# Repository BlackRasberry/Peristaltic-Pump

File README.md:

# Peristaltic-Pump
An open source peristaltic pump

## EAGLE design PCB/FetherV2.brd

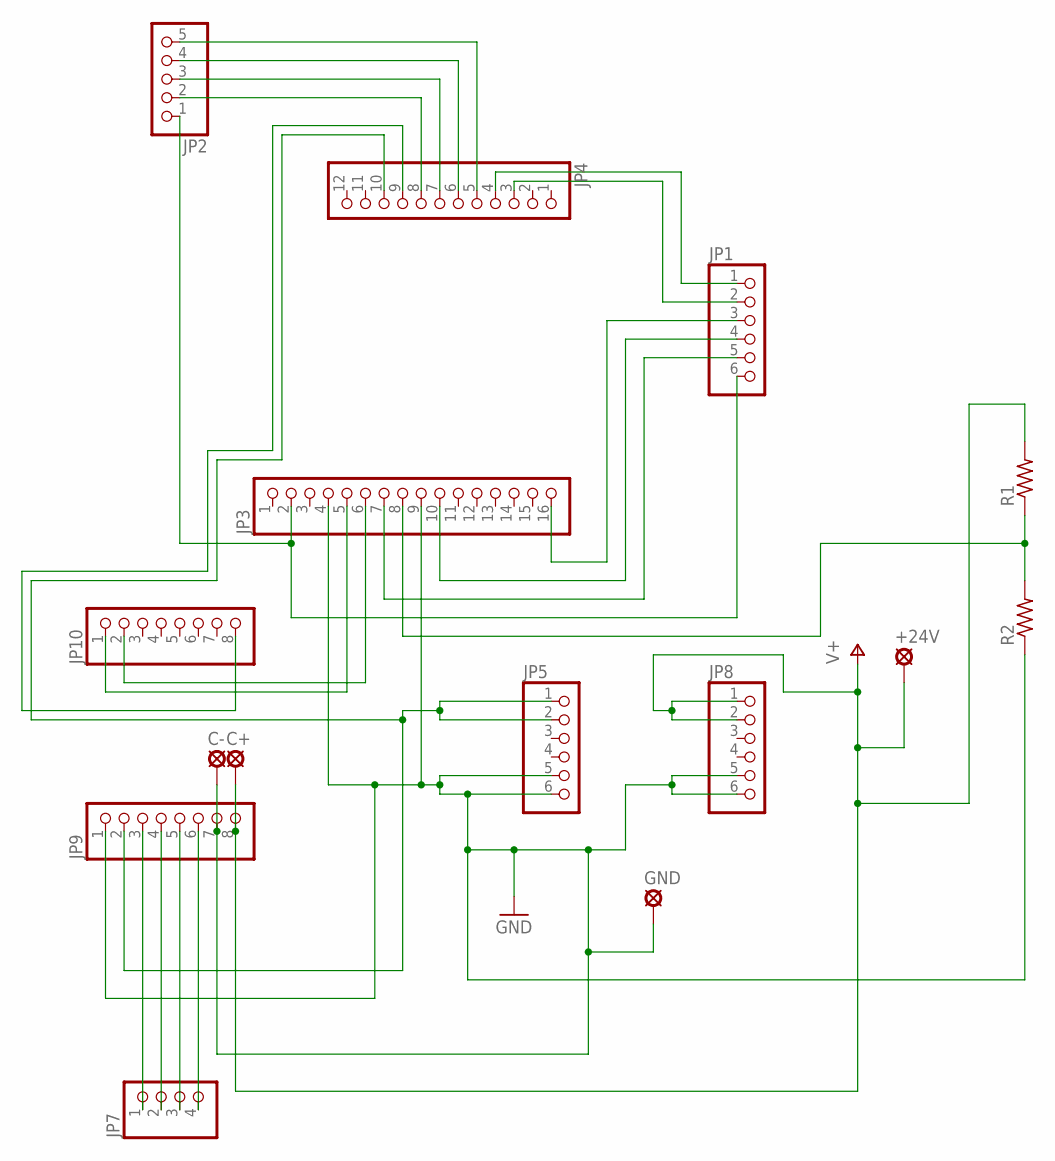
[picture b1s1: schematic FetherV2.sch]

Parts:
+24V: SE14
C+: SE14
C-: SE14
GND: SE14
JP1: PINHD-1X6/90; 1X06/90
JP2: PINHD-1X5/90; 1X05/90
JP3: PINHD-1X16; 1X16
JP4: PINHD-1X12; 1X12
JP5, JP8: PINHD-1X6; 1X06
JP7: PINHD-1X4; 1X04
JP9, JP10: PINHD-1X8; 1X08
R1, R2: FLIPFLOP-RES; 0805-THM

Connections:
GND: C-.MP, GND.MP, JP3.4, JP3.9, JP5.5, JP5.6, JP8.5, JP8.6, JP9.1, JP9.7, R2.1
unnamed: JP2.2, JP4.8
unnamed: JP2.3, JP4.7
unnamed: JP2.4, JP4.6
unnamed: JP2.5, JP4.5
unnamed: JP1.1, JP4.4
unnamed: JP1.2, JP4.3
unnamed: JP7.1, JP9.3
unnamed: JP1.3, JP3.16
unnamed: JP1.4, JP3.10
unnamed: JP1.5, JP3.7
unnamed: JP1.6, JP2.1, JP3.2
unnamed: JP4.10, JP5.1, JP5.2, JP9.2
unnamed: JP7.2, JP9.4
unnamed: JP7.3, JP9.5
unnamed: JP7.4, JP9.6
unnamed: JP3.5, JP10.1
unnamed: JP4.9, JP10.8
unnamed: JP3.6, JP10.2
unnamed: JP3.8, R1.1, R2.2
V+: +24V.MP, C+.MP, JP8.1, JP8.2, JP9.8, R1.2

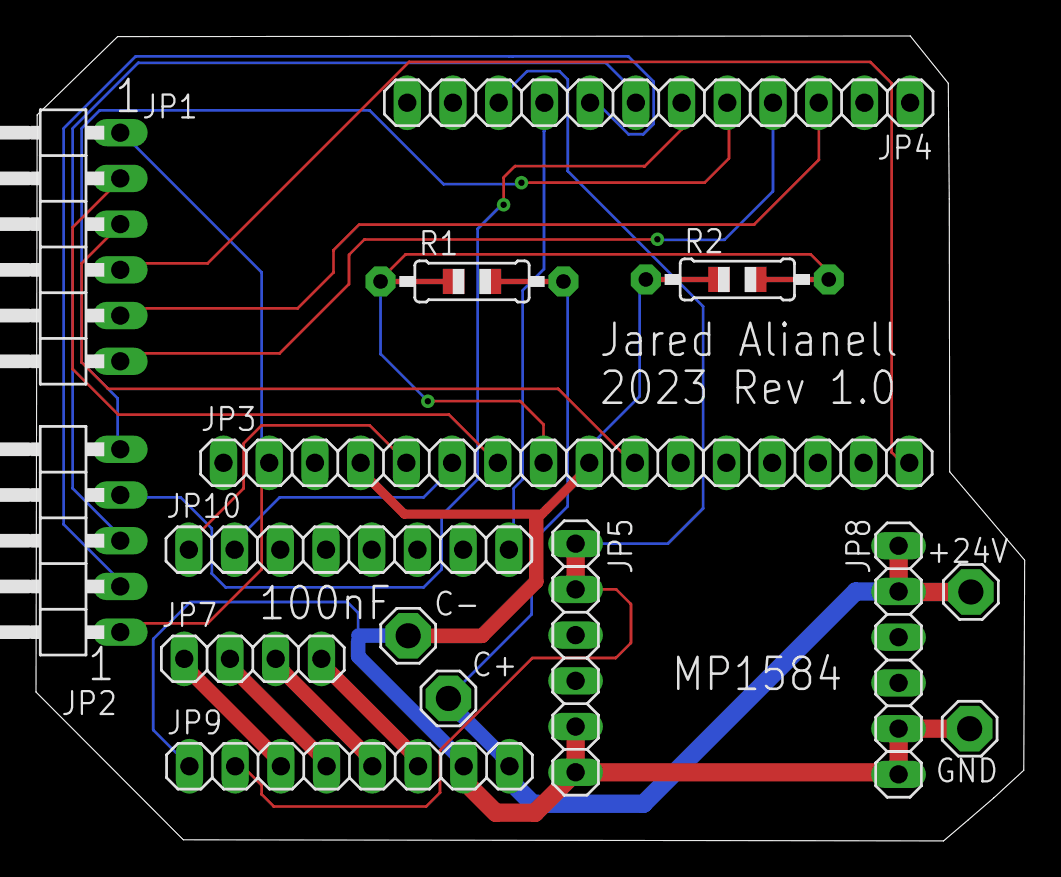
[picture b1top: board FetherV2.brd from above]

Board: 2 copper layers, 54.9 x 44.7 mm, 15 parts (0 on the bottom side), 21 nets.

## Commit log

2023-12-26 Add files via upload
    Main ESP Code
2023-12-26 Add files via upload
    All PCB version files. Use "Feather_V2_REV1.brd" for editing
